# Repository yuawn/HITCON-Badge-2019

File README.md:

# HITCON Badge 2019
## Overview
HITCON Badge 2019 is based on `M2351ZIAAE` MCU. 
## Usage
There are four pages, you can use `LEFT` and `RIGHT` button on the badge to switch them.
### Page 0: LED Level Display
* Badge will show the status of 24 LEDs.
    * Locked: white color
    * Unlocked: Bright and colorful
* Press `UP` + `A`/`B` to decrease/increase the brightness.
* You can unlock each LED by playing the game or completing the mission with sponsors.
### Page 1: Pattern Display
* Use `UP` and `DOWN` button to select patterns.
* Pattern 0 will be unlocked by unlocking led 0 1 2.
    * Pattern 1: led 3 4 5.
    * Pattern 2: led 6 7 8.
    * ..
* If the pattern is still locked, it will render the error pattern (all LED are red).
* There are 11 patterns in total.
### Page 2: Paint Mode
* In this page, you can customize the color of LEDs!
* Select the LEDs by pressing `UP` `DOWN` `LEFT` `RIGHT`.
* Change the color by pressing `A` `B`.
* Press `AB` (at the same time) and then press `LEFT`/`RIGHT` to leave paint mode.
### Page 3: Snake
```
################################
#                              #
#                              #                                   
#                              #                                   
#                              #                                   
#                              #                                   
#                              #                                   
#                              #                                   
#      @@@@@@@          o      #                                   
#                              #                                   
#                              #                                   
#                              #                                   
#                              #                                   
#                              #
#                              #
#                              # 
#                              #
################################
[Score] 6 pt
```
* Let badge connect to the computor with Micro USB cable.
* Use any client you like to connect the serial com port.
    * Linux/macOS: You can use `screen` command.
        * example: `screen /dev/tty.usbmodemxxx` (replace `/dev/tty.usbmodemxxx` with correct path)
    * Windows: You can use `PuTTY` (Connection type: Serial) to connect the COM port.
* Control the snake by pressing `UP` `DOWN` `LEFT` `RIGHT`.
* Press `AB` at the same time to pause the game.
    * Press `AB` again to continue the game, `LEFT` to exit.
* Score
    * score >= 50, snake pattern (pattern 8) will unlocked!
    * score == 2147483647: Well done, hacker :)
## Badge Command Line
```
  _  _ ___ _____ ___ ___  _  _   ___ __  _ ___
 | || |_ _|_   _/ __/ _ \| \| | |_  )  \/ / _ \
 | __ || |  | || (_| (_) | .` |  / / () | \_, /
 |_||_|___| |_| \___\___/|_|\_| /___\__/|_|/_/

HitconBadge2019 >>
```
* There is a simple command line interface running on the badge.
* You can use it by connecting the badge to computer with micro usb.
### Commands
#### help
Type help for all available commands.
```
HitconBadge2019 >> help
show
info
unlock
setname
clear
hello
angelboy
yuawn
ping
ls
id
cat
echo
alias
whoami
help
```
#### show
Show command will display the status of all LEDs and patterns.
```
HitconBadge2019 >> show
Pattern 0: Lock
  led 00: Lock
  led 01: Lock
  led 02: Lock
Pattern 1: Lock
  led 03: Lock
  led 04: Lock
  led 05: Lock
Pattern 2: Lock
  led 06: Lock
  led 07: Lock
  led 08: Lock
Pattern 3: Lock
  led 09: Lock
  led 10: Lock
  led 11: Lock
Pattern 4: Lock
  led 12: Lock
  led 13: Lock
  led 14: Lock
Pattern 5: Lock
  led 15: Lock
  led 16: Lock
  led 17: Lock
Pattern 6: Lock
  led 18: Lock
  led 19: Lock
  led 20: Lock
Pattern 7: Lock
  led 21: Lock
  led 22: Lock
  led 23: Lock

Badge challenge:
[Stage 1] Snake pattern: Lock
[Stage 2] Pwned NS pattern: Lock
[Stage 3] Pwned the whole badge pattern: Lock
```
## HITCON Badge Challenges
> Badge source code, solution and exploits will be released within the talk `HITCON Badge 2019 秘辛: MCU ARM TrustZone challenges` at R0 (Day2 14:40 - 15:30).

There are 11 pattern in total, but three of them are special, so you need to get them in special way :)
### Stage 0 - Warm Up
* Before pwning the badge, why not play some game first.
* Get the score higher than 50, you can unlock the snake pattern.
### Stage 1 - Hack The Game
* Try to let the score == 2147483647 by playing the game.
* Or pwn the badge :)
* You will know how to do it by reversing the binary of normal world (NonSecure world) in this MCU TrustZone.
* To make life easier, the binary is not striped and not a raw binary, just take them all (See `firmware/`)
### Stage 2 - Pwn the Badge
* The final target is protected by TrustZone in Secure Region.
* I put my secret in the TrustZone, it is pretty safe, isn't it?
* Try to pwn the badge for all patterns!

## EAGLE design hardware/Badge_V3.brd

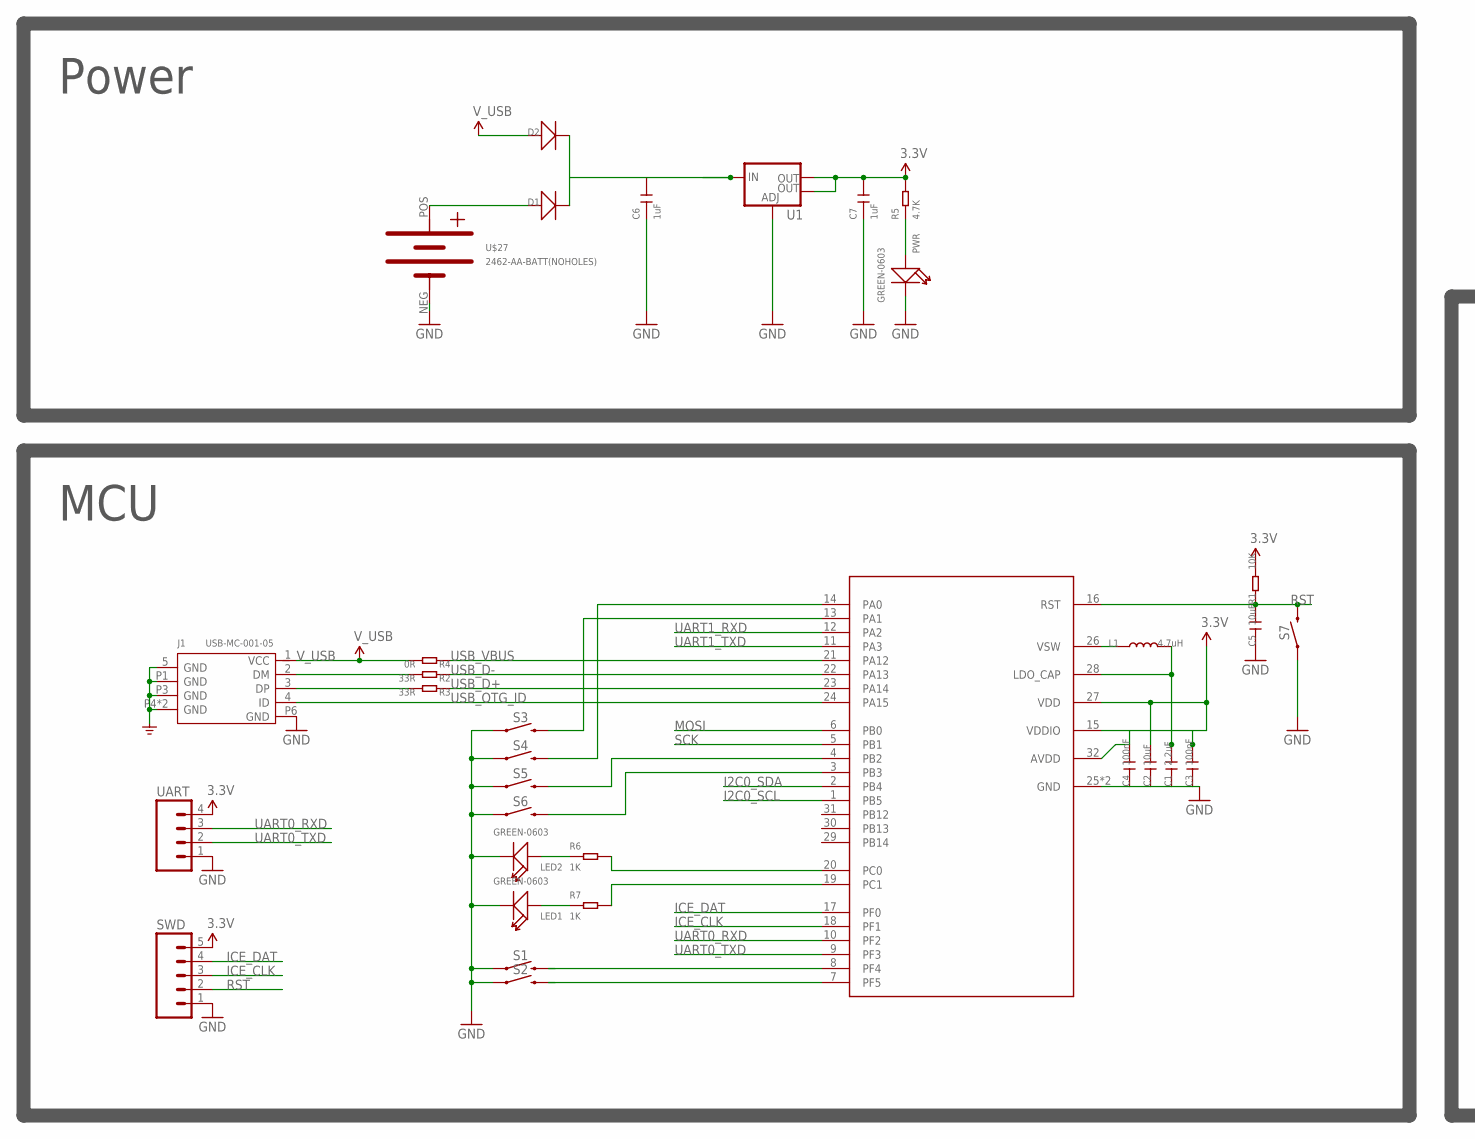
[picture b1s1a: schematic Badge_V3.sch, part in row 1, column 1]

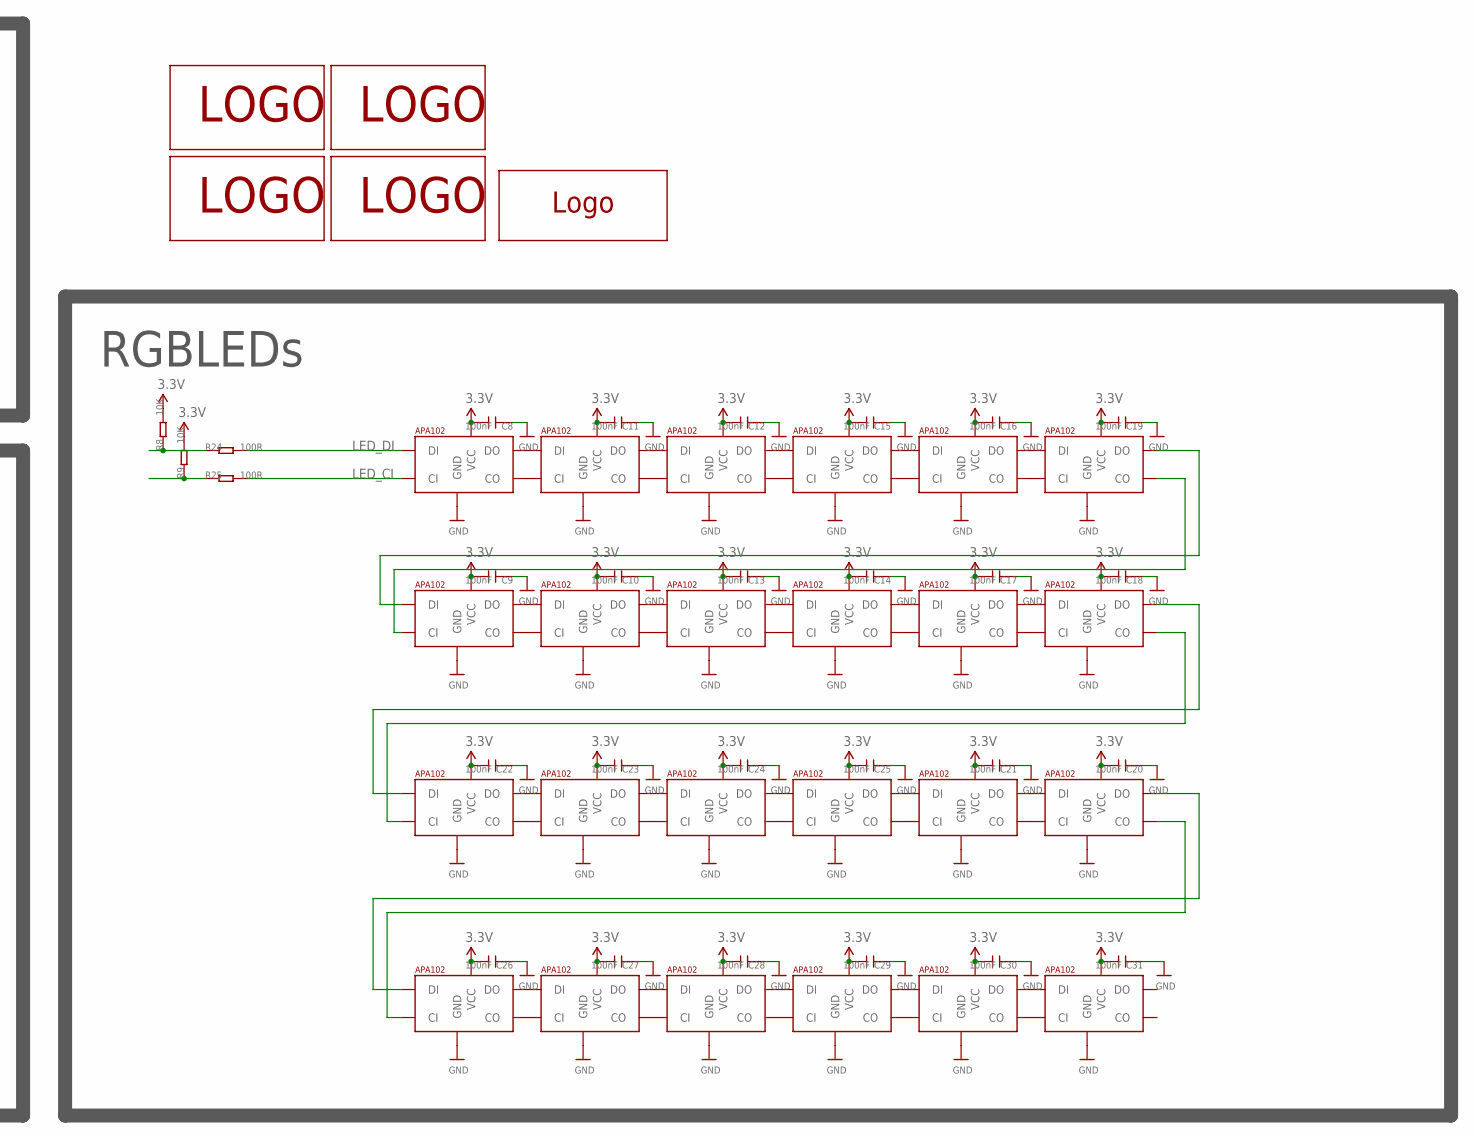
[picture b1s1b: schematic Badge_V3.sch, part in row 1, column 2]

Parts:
C1: 2.2uF; C0402@1
C2, C5: 10uF; C0402@1
C3: 100nF; C0603@1
C4, C8, C9, C10, C11, C12, C13, C14, C15, C16, C17, C18, C19, C20, C21, C22, C23, C24, C25, C26, C27, C28, C29, C30, C31: 100nF; C0402@1
C6, C7: 1uF; C0603
D1, D2: D'1206'; SOD123
J1: USB-MC-001-05; MICRO-USB5+5P-SMD-0.65-7.2X5.06MM
L1: 4.7uH; L0603
LED1, LED2: GREEN-0603; LED-0603
PWR: GREEN-0603; LED-0603
R1, R8, R9: 10K; R0402
R2, R3: 33R; R0402
R4: 0R; R0402
R5: 4.7K; R0402
R6, R7: 1K; R0402
R24, R25: 100R; R0402
S1, S2, S3, S4, S5, S6, S7: MOMENTARY-SWITCH-SPST-SMD-6.2MM-TALL; TACTILE_SWITCH_SMD_6.2MM_TALL
SWD: M05LOCK; 1X05_LOCK
U1: V_REG_LM1117SOT223; SOT223
U$1: M2351; QFN-32
U$2, U$4, U$5, U$6, U$7, U$8, U$9, U$10, U$11, U$12, U$13, U$14, U$15, U$16, U$17, U$18, U$19, U$20, U$21, U$22, U$23, U$24, U$25, U$33: APA1022020; APA102_2020
U$26: TAIWANSILK_FILL; TAIWAN_SILK_FILL
U$27: 2462-AA-BATT(NOHOLES); 2462-AA-BATT-NOHOLES
U$28: HITCON_LOGOGOLD_LARGE; HITCON_LOGO_BIGGER_GOLD
U$30: TAIWANKIM; TAIWAN_SILK_FILL_2
U$31: TAIWANMAZ; TAIWAN_SILK_FILL_4
U$34: TAIWANPUN; TAIWAN_SILK_FILL_3
UART: M04LOCK; 1X04_LOCK

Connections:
3.3V: C2.2, C3.2, C4.2, C7.2, C8.2, C9.2, C10.2, C11.2, C12.2, C13.2, C14.2, C15.2, C16.2, C17.2, C18.2, C19.2, C20.2, C21.2, C22.2, C23.2, C24.2, C25.2, C26.2, C27.2, C28.2, C29.2, C30.2, C31.2, R1.2, R5.2, R8.2, R9.2, SWD.5, U1.2 (OUT), U1.4 (OUT), U$1.15 (VDDIO), U$1.27 (VDD), U$1.32 (AVDD), U$2.V_CC (VCC), U$4.V_CC (VCC), U$5.V_CC (VCC), U$6.V_CC (VCC), U$7.V_CC (VCC), U$8.V_CC (VCC), U$9.V_CC (VCC), U$10.V_CC (VCC), U$11.V_CC (VCC), U$12.V_CC (VCC), U$13.V_CC (VCC), U$14.V_CC (VCC), U$15.V_CC (VCC), U$16.V_CC (VCC), U$17.V_CC (VCC), U$18.V_CC (VCC), U$19.V_CC (VCC), U$20.V_CC (VCC), U$21.V_CC (VCC), U$22.V_CC (VCC), U$23.V_CC (VCC), U$24.V_CC (VCC), U$25.V_CC (VCC), U$33.V_CC (VCC), UART.4
GND: C1.1, C2.1, C3.1, C4.1, C5.1, C6.1, C7.1, C8.1, C9.1, C10.1, C11.1, C12.1, C13.1, C14.1, C15.1, C16.1, C17.1, C18.1, C19.1, C20.1, C21.1, C22.1, C23.1, C24.1, C25.1, C26.1, C27.1, C28.1, C29.1, C30.1, C31.1, J1.5 (GND), J1.P1 (GND), J1.P3 (GND), J1.P4 (GND), J1.P5 (GND), J1.P6 (GND), LED1.-, LED2.-, PWR.-, S1.A2 (1), S2.A2 (1), S3.A2 (1), S4.A2 (1), S5.A2 (1), S6.A2 (1), S7.A2 (1), SWD.1, U1.1 (ADJ), U$1.25 (GND), U$1.EP (GND), U$2.GND, U$4.GND, U$5.GND, U$6.GND, U$7.GND, U$8.GND, U$9.GND, U$10.GND, U$11.GND, U$12.GND, U$13.GND, U$14.GND, U$15.GND, U$16.GND, U$17.GND, U$18.GND, U$19.GND, U$20.GND, U$21.GND, U$22.GND, U$23.GND, U$24.GND, U$25.GND, U$27.NEG, U$33.GND, UART.1
I2C0_SCL: U$1.1 (PB5)
I2C0_SDA: U$1.2 (PB4)
ICE_CLK: SWD.3, U$1.18 (PF1)
ICE_DAT: SWD.4, U$1.17 (PF0)
LED_CI: R25.2, U$33.C_IN (CI)
LED_DI: R24.2, U$33.D_IN (DI)
MOSI: R8.1, R24.1, U$1.6 (PB0)
unnamed: L1.1, U$1.26 (VSW)
unnamed: C1.2, L1.2, U$1.28 (LDO_CAP)
unnamed: J1.2 (DM), R2.2
unnamed: J1.3 (DP), R3.2
unnamed: R6.2, U$1.20 (PC0)
unnamed: C6.2, D1.-, D2.-, U1.3 (IN)
unnamed: PWR.+, R5.1
unnamed: D1.+, U$27.POS
unnamed: S1.B2 (2), U$1.8 (PF4)
unnamed: S2.B2 (2), U$1.7 (PF5)
unnamed: S4.B2 (2), U$1.14 (PA0)
unnamed: LED2.+, R6.1
unnamed: LED1.+, R7.1
unnamed: R7.2, U$1.19 (PC1)
unnamed: S3.B2 (2), U$1.13 (PA1)
unnamed: S5.B2 (2), U$1.4 (PB2)
unnamed: S6.B2 (2), U$1.3 (PB3)
unnamed: U$2.D_OUT (DO), U$4.D_IN (DI)
unnamed: U$2.CL_OUT (CO), U$4.C_IN (CI)
unnamed: U$4.CL_OUT (CO), U$5.C_IN (CI)
unnamed: U$4.D_OUT (DO), U$5.D_IN (DI)
unnamed: U$5.D_OUT (DO), U$6.D_IN (DI)
unnamed: U$5.CL_OUT (CO), U$6.C_IN (CI)
unnamed: U$6.CL_OUT (CO), U$7.C_IN (CI)
unnamed: U$6.D_OUT (DO), U$7.D_IN (DI)
unnamed: U$8.D_OUT (DO), U$9.D_IN (DI)
unnamed: U$8.CL_OUT (CO), U$9.C_IN (CI)
unnamed: U$9.CL_OUT (CO), U$10.C_IN (CI)
unnamed: U$9.D_OUT (DO), U$10.D_IN (DI)
unnamed: U$10.D_OUT (DO), U$11.D_IN (DI)
unnamed: U$10.CL_OUT (CO), U$11.C_IN (CI)
unnamed: U$11.CL_OUT (CO), U$12.C_IN (CI)
unnamed: U$11.D_OUT (DO), U$12.D_IN (DI)
unnamed: U$12.D_OUT (DO), U$13.D_IN (DI)
unnamed: U$12.CL_OUT (CO), U$13.C_IN (CI)
unnamed: U$14.CL_OUT (CO), U$15.C_IN (CI)
unnamed: U$14.D_OUT (DO), U$15.D_IN (DI)
unnamed: U$15.D_OUT (DO), U$16.D_IN (DI)
unnamed: U$15.CL_OUT (CO), U$16.C_IN (CI)
unnamed: U$16.CL_OUT (CO), U$17.C_IN (CI)
unnamed: U$16.D_OUT (DO), U$17.D_IN (DI)
unnamed: U$17.D_OUT (DO), U$18.D_IN (DI)
unnamed: U$17.CL_OUT (CO), U$18.C_IN (CI)
unnamed: U$18.CL_OUT (CO), U$19.C_IN (CI)
unnamed: U$18.D_OUT (DO), U$19.D_IN (DI)
unnamed: U$2.C_IN (CI), U$33.CL_OUT (CO)
unnamed: U$2.D_IN (DI), U$33.D_OUT (DO)
unnamed: U$20.D_OUT (DO), U$21.D_IN (DI)
unnamed: U$20.CL_OUT (CO), U$21.C_IN (CI)
unnamed: U$21.D_OUT (DO), U$22.D_IN (DI)
unnamed: U$21.CL_OUT (CO), U$22.C_IN (CI)
unnamed: U$22.D_OUT (DO), U$23.D_IN (DI)
unnamed: U$22.CL_OUT (CO), U$23.C_IN (CI)
unnamed: U$23.D_OUT (DO), U$24.D_IN (DI)
unnamed: U$23.CL_OUT (CO), U$24.C_IN (CI)
unnamed: U$24.D_OUT (DO), U$25.D_IN (DI)
unnamed: U$24.CL_OUT (CO), U$25.C_IN (CI)
unnamed: U$7.D_OUT (DO), U$8.D_IN (DI)
unnamed: U$7.CL_OUT (CO), U$8.C_IN (CI)
unnamed: U$13.D_OUT (DO), U$14.D_IN (DI)
unnamed: U$13.CL_OUT (CO), U$14.C_IN (CI)
unnamed: U$19.D_OUT (DO), U$20.D_IN (DI)
unnamed: U$19.CL_OUT (CO), U$20.C_IN (CI)
RST: C5.2, R1.1, S7.B2 (2), SWD.2, U$1.16 (RST)
SCK: R9.1, R25.1, U$1.5 (PB1)
UART0_RXD: U$1.10 (PF2), UART.3
UART0_TXD: U$1.9 (PF3), UART.2
UART1_RXD: U$1.12 (PA2)
UART1_TXD: U$1.11 (PA3)
USB_D+: R3.1, U$1.23 (PA14)
USB_D-: R2.1, U$1.22 (PA13)
USB_OTG_ID: J1.4 (ID), U$1.24 (PA15)
USB_VBUS: R4.1, U$1.21 (PA12)
V_USB: D2.+, J1.1 (VCC), R4.2

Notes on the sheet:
MCU
Power
RGBLEDs

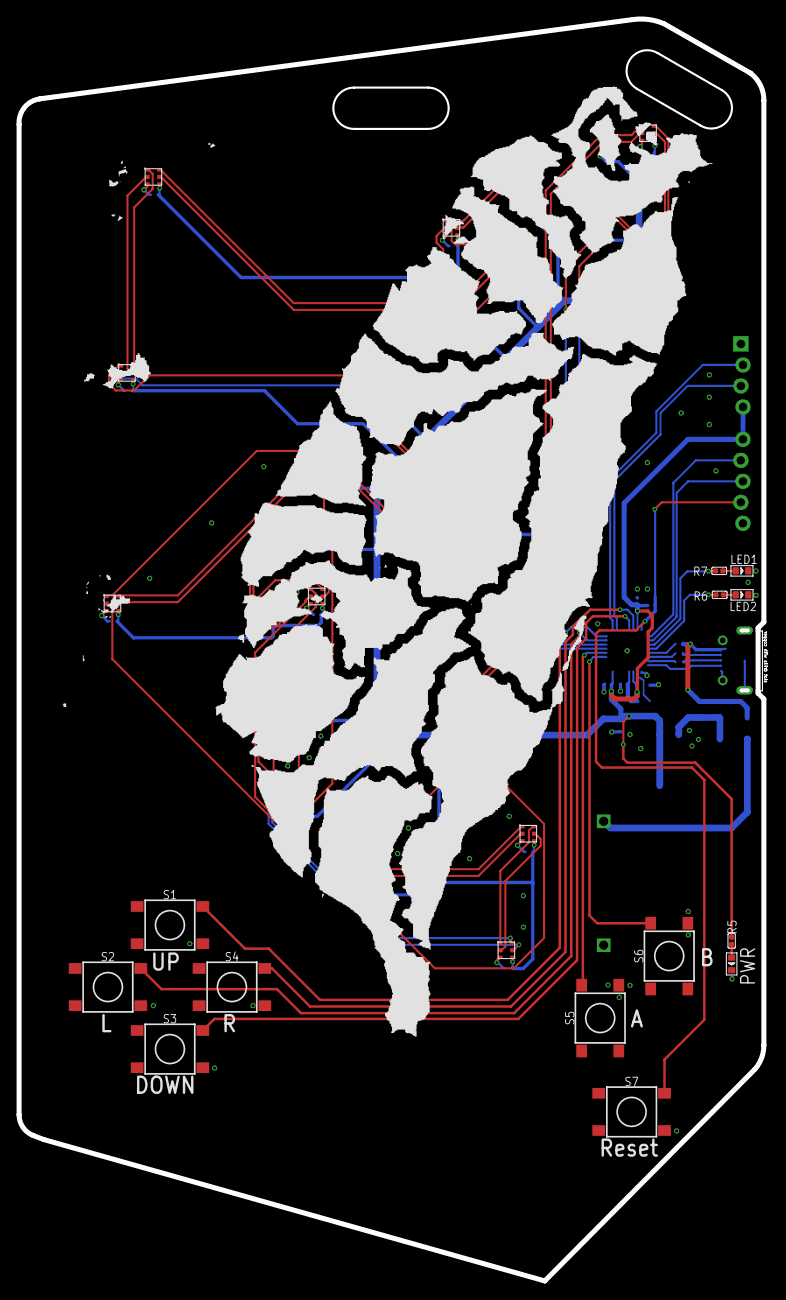
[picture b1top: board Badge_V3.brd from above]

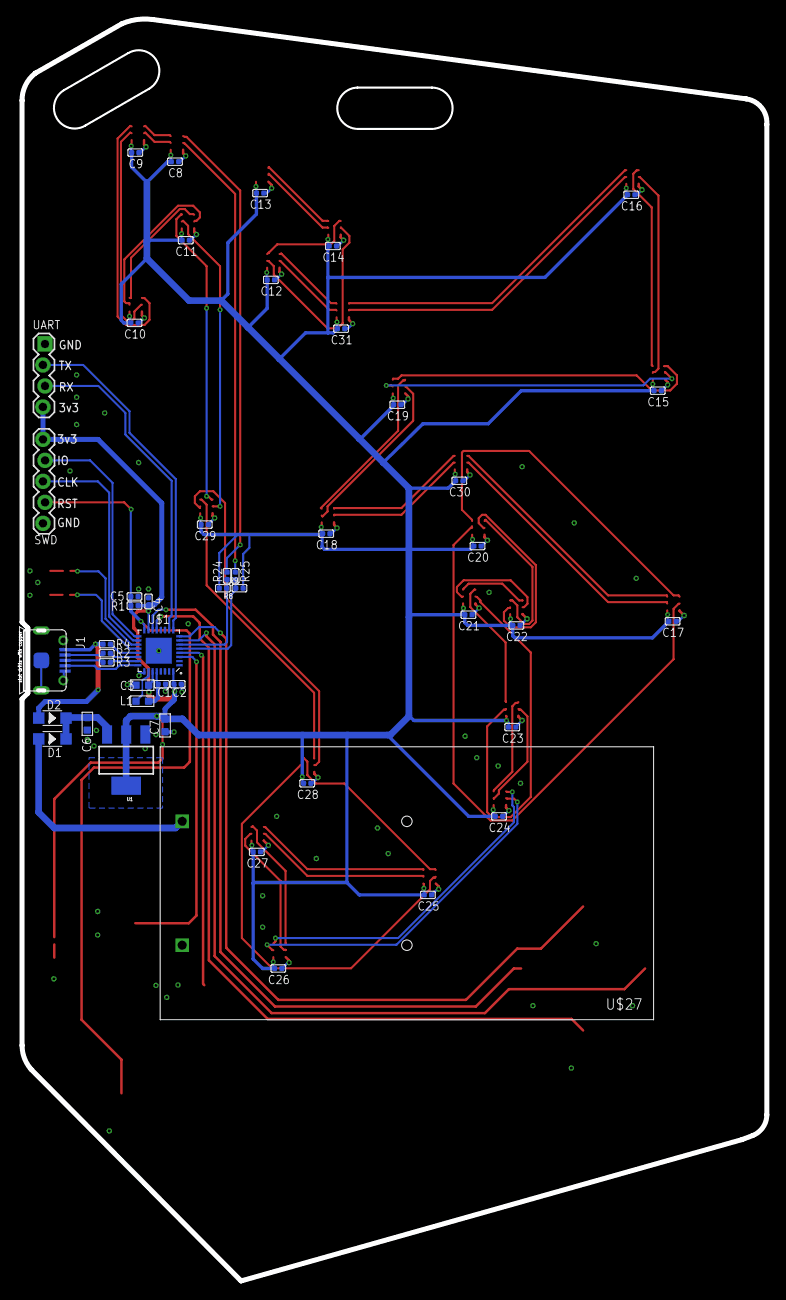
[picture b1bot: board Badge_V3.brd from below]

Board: 2 copper layers, 90.5 x 152.7 mm, 90 parts (48 on the bottom side), 79 nets.

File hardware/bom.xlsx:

Qty | Value | Package | Parts | Description
2 |  | SOD323 | D1, D2 | Diode
1 | 0R | R0402 | R4 | Resistor
2 | 100R | R0402 | R24, R25 | Resistor
25 | 100nF | C0402 | C4, C8, C9, C10, C11, C12, C13, C14, C15, C16, C17, C18, C19, C20, C21, C22, C2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 | Ceramic Capacitors
1 | 100nF | C0603 | C3 | Ceramic Capacitors
3 | 10K | R0402 | R1, R8, R9 | Resistor
2 | 10uF | C0402 | C2, C5 | Ceramic Capacitors
2 | 1K | R0402 | R6, R7 | Resistor
2 | 1uF | C0603 | C6, C7 | Ceramic Capacitors
1 | 2.2uF | C0402 | C1 | Ceramic Capacitors
1 | 2462-AA-BATT(NOHOLES) | 2462-AA-BATT-NOHOLES | U$27 | Battery Holder
2 | 33R | R0402 | R2, R3 | Resistor
1 | 4.7K | R0402 | R5 | Resistor
1 | 4.7uH | L0603 | L1 | Inductor
24 | APA102-2020 | APA102_2020 | U$2, U$4, U$5, U$6, U$7, U$8, U$9, U$10, U$11, U$12, U$13, U$14, U$15, U$16, U$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 | APA102C 5050 RGB LED
3 | GREEN-0603 | LED-0603 | LED1, LED2, PWR | LED
1 | M2351 | QFN-32 | U$1 | MCU
7 | MOMENTARY-SWITCH-SPST-SMD-6.2MM-TALL | 6.2MMX6.2MM_Swtich | S1, S2, S3, S4, S5, S6, S7 | Switch
1 | USB-MC-001-05 | MICRO-USB5+5P-SMD-0.65-7.2X5.06MM | J1
1 | LM1117-3.3v | SOT-223 | U1 | LDO

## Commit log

2019-08-23 add readme
2019-08-23 release non-secure firmware
2019-08-23 add license
2019-08-23 Fix typo
2019-08-24 badge is now open source!
2019-08-25 Adding Hardware
2019-08-25 Added HITCON CMT slide.
2019-08-27 Released seucre firmware, hex and icp file
2019-08-28 Updated exploits.

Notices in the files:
parts and their libraries:
SparkFun-Connectors: Licensing: Creative Commons ShareAlike 4.0 International - https://creativecommons.org/licenses/by-sa/4.0
microbuilder: This work is placed in the public domain, and may be freely used for commercial and non-commercial work with the following conditions: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
